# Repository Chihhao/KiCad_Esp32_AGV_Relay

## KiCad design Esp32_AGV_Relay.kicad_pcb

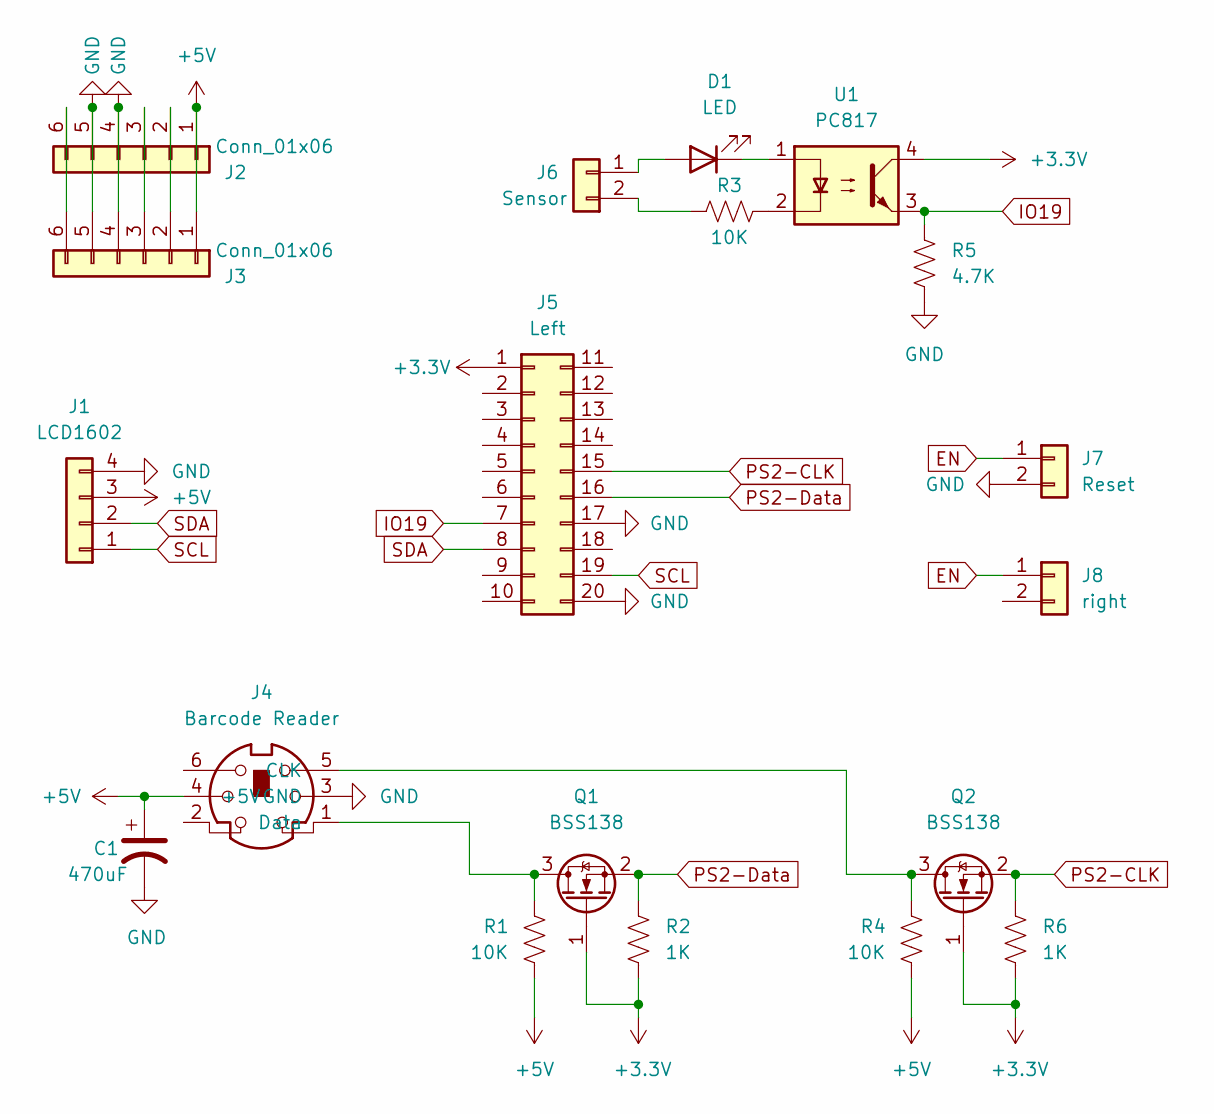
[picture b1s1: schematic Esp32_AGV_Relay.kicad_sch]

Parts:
C1: 470uF; CP_Radial_D10.0mm_P5.00mm
D1: LED; LED_0805_2012Metric
J1: LCD1602; Molex_KK-254_AE-6410-04A_1x04_P2.54mm_Vertical
J2, J3: Conn_01x06; PinSocket_1x06_P2.54mm_Vertical
J4: Barcode Reader; Connector_Mini-DIN_Female_6Pin_2rows
J5: Left; PinSocket_2x10_P2.54mm_Vertical
J6: Sensor; TerminalBlock_Phoenix_MKDS-1,5-2-5.08_1x02_P5.08mm_Horizont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
J7: Reset; Molex_KK-254_AE-6410-02A_1x02_P2.54mm_Vertical
J8: right; PinSocket_1x02_P2.54mm_Vertical
Q1, Q2: BSS138; SOT-23
R1, R3, R4: 10K; R_0805_2012Metric
R2, R6: 1K; R_0805_2012Metric
R5: 4.7K; R_0805_2012Metric
U1: PC817; DIP-4_W7.62mm

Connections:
+3.3V: J5.1, Q1.1 (G), Q2.1 (G), R2.1, R6.1, U1.4
+5V: C1.1, J1.3, J2.1, J3.1, J4.4 (+5V), R1.1, R4.1
EN: J7.1, J8.1
GND: C1.2, J1.4, J2.4, J2.5, J3.4, J3.5, J4.3 (GND), J5.17, J5.20, J7.2, R5.1
IO19: J5.7, R5.2, U1.3
unnamed: D1.1 (K), U1.1
unnamed: D1.2 (A), J6.1 (Pin_2)
unnamed: J2.2, J3.2
unnamed: J2.3, J3.3
unnamed: J2.6, J3.6
unnamed: J4.1 (Data), Q1.3 (D), R1.2
unnamed: J4.5 (CLK), Q2.3 (D), R4.2
unnamed: J6.2 (Pin_1), R3.2
unnamed: R3.1, U1.2
PS2-CLK: J5.15, Q2.2 (S), R6.2
PS2-Data: J5.16, Q1.2 (S), R2.2
SCL: J1.1, J5.19
SDA: J1.2, J5.8

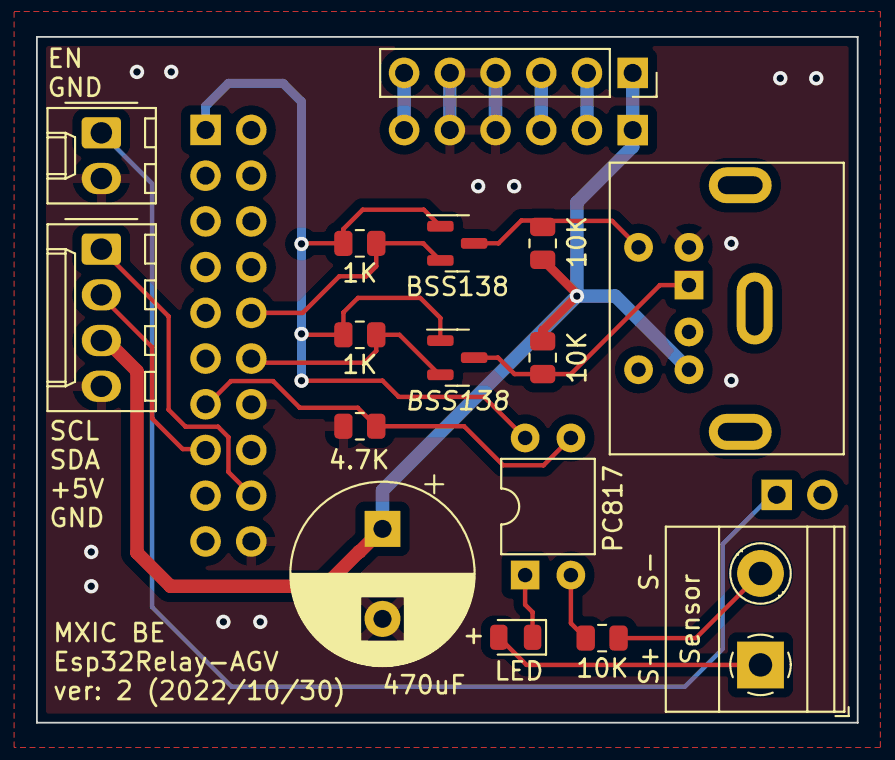
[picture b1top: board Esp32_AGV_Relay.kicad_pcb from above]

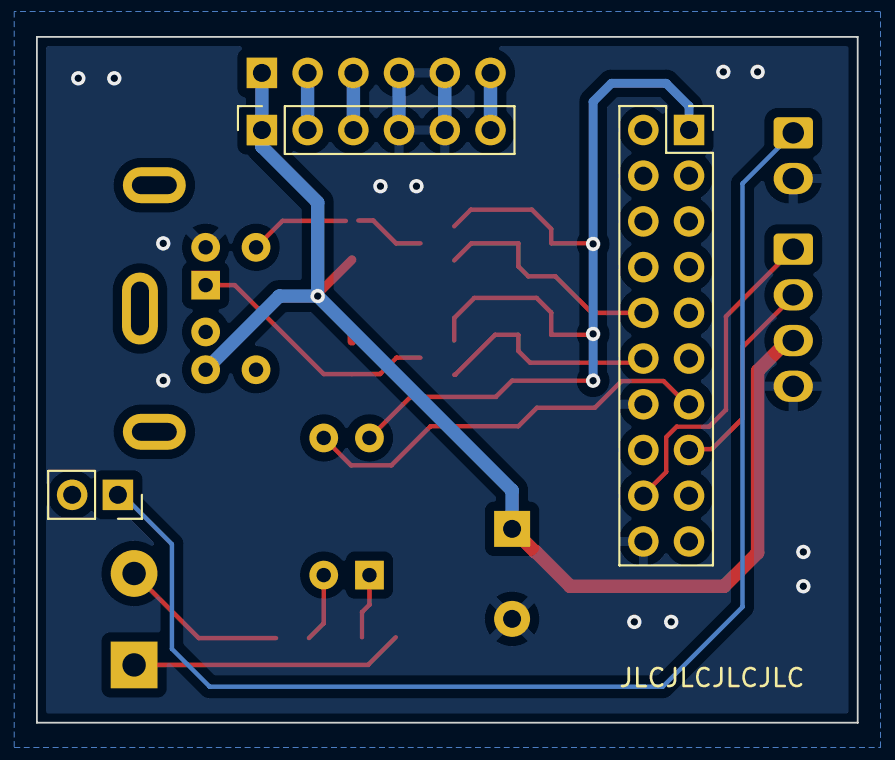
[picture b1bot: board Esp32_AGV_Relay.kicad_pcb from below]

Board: 2 copper layers, 45.6 x 38.1 mm, 19 parts (3 on the bottom side), 18 nets.

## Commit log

2022-10-30 v2
    1. 改成下拉電阻
    2. 更換連接器
